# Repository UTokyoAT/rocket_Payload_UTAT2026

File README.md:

# rocket_Payload_UTAT2026

輸送機班2026年度の新人研修期間中の上級生での活動。CanSatを搭載したペットボトルロケットを開発するためのリポジトリ

---

## ドキュメント

- [環境構築](docs/setup.md)（未作成）
- [書き込み方法](docs/flashing.md)（未作成）
- [制御構造・アーキテクチャ](docs/architecture.md)（未作成）
- [地上局セットアップ](docs/ground-station.md)（未作成）
- [JLCPCB 発注手順](docs/pcb-ordering.md)（未作成）

---

## ディレクトリ構造

Seeed XIAO ESP32-S3 を1枚使う構成。ミッション本体は `env:mission`（`tests/test_mission/main.cpp`）。

```
rocket_Payload_UTAT2026/
│
├── platformio.ini           # ビルド・ボード・ライブラリ設定（env:mission / env:test-* ）
│
├── include/
│   └── secrets.example.h    # Wi-Fi・MQTT接続設定のひな形（secrets.h にコピーして使う）
│
├── src/
│   ├── MotorController/     # 単純な方位PID → 左右PWMの差動
│   ├── Actuator/            # モーター制御（TB6612FNG）
│   ├── Deployer/            # ロケット分離・パラシュート分離（ニクロム線）
│   └── LED/                 # LED制御
│
├── lib/
│   ├── Encoder/             # 左右ホイールエンコーダ（ホール、A/B相の割り込みカウント）
│   ├── Expander/            # I/Oエキスパンダ（MCP23008）
│   ├── GPS/                 # TinyGPSPlus ラッパー
│   ├── KalmanFilter/        # 拡張カルマンフィルタ（EKF）
│   ├── Sensor/              # BMP280・MPU6050 ドライバ
│   └── Telemetry/           # Wi-Fi + MQTT で地上局へ送信
│
├── tests/
│   ├── test_mission/        # ミッション本体（キャリブレーション → EKF起動 → 誘導 → 停止）
│   └── test_*/              # センサー・アクチュエータ単体の動作確認（env:test-*）
│
├── matlab/
│   └── ekf_cansat_simulation/  # EKF・誘導のシミュレーション（符号規約の参照実装）
│
├── ground/
│   └── server/              # 地上局（Mosquitto・Telegraf・InfluxDB・Grafana の docker compose）
│
└── hardware/
    ├── kicad/               # KiCad プロジェクトファイル
    └── jlcpcb/
        ├── gerbers/         # Gerberファイル（発注用ZIP）
        ├── bom/             # Bill of Materials
        └── cpl/             # Component Placement List
```

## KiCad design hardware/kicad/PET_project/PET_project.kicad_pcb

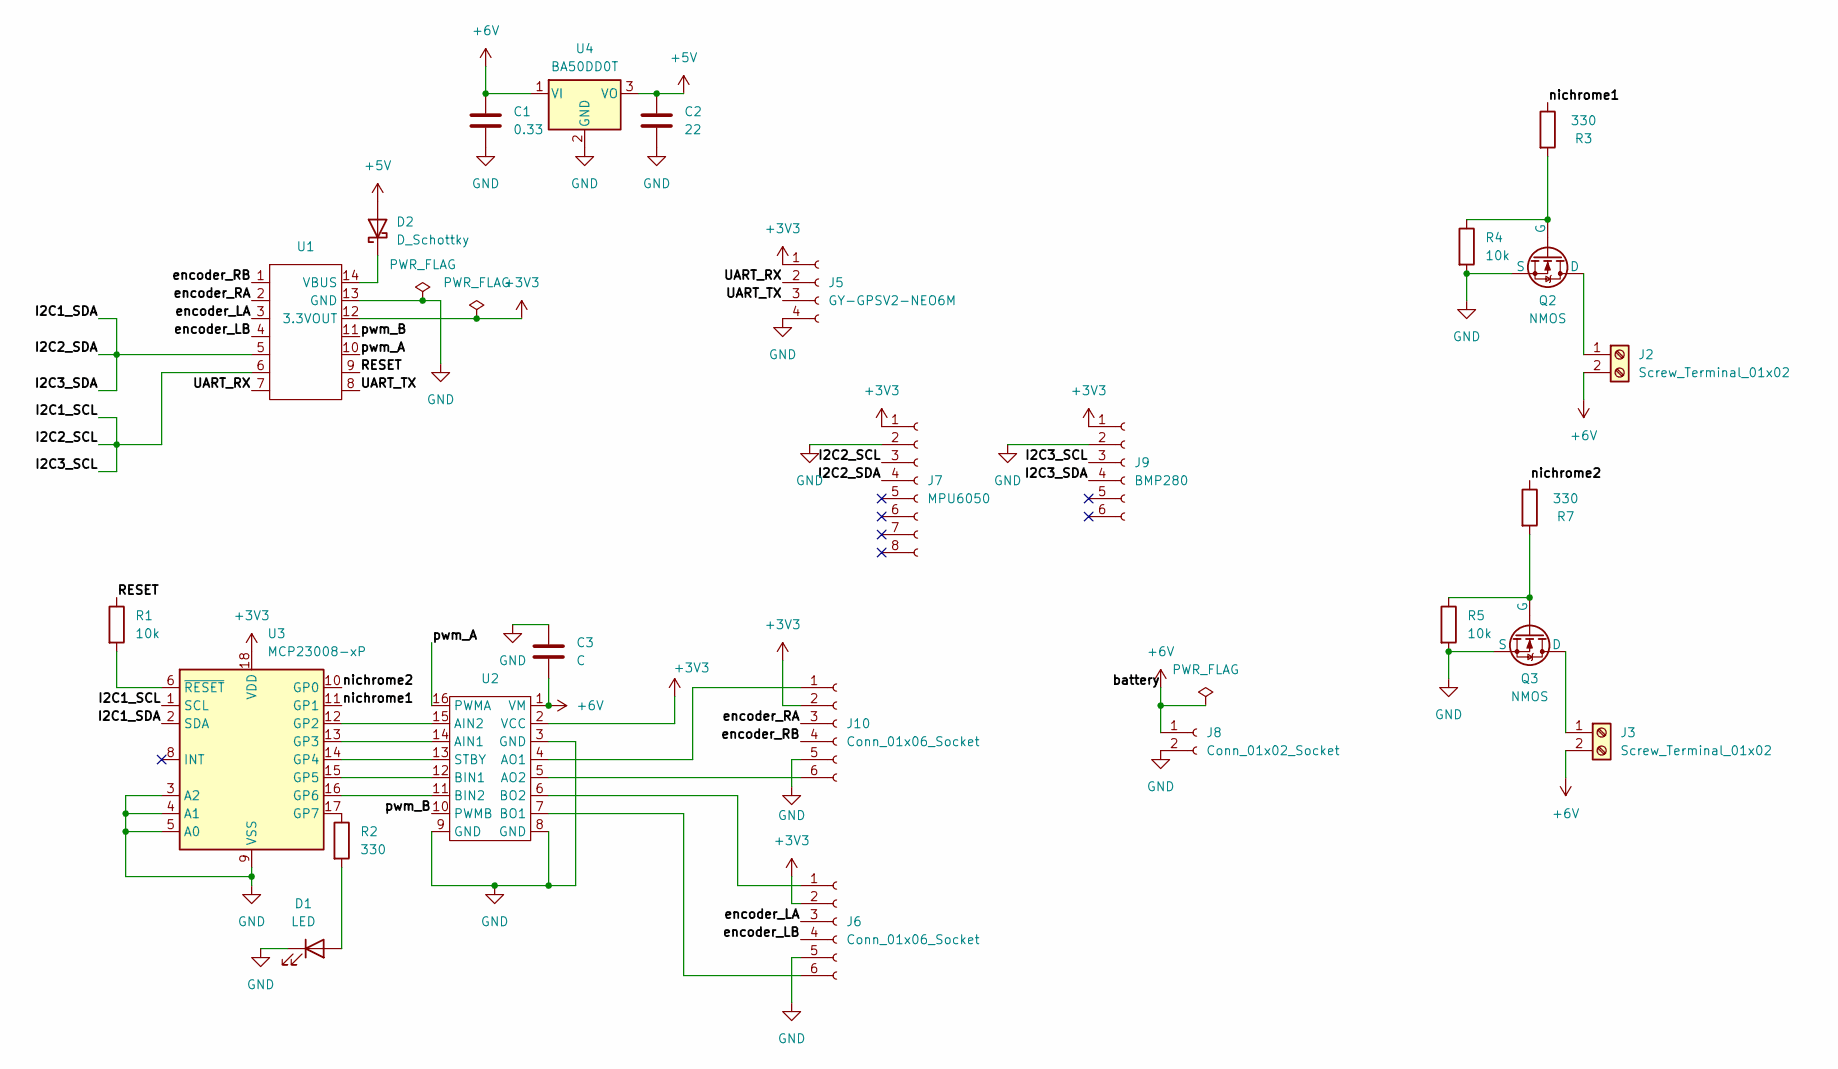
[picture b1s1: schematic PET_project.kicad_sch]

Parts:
C1: 0.33; CP_Radial_Tantal_D4.5mm_P5.00mm
C2: 22; C_Radial_D5.0mm_H11.0mm_P2.00mm
C3: C; CP_Radial_D6.3mm_P2.50mm
D1: LED; LED_D5.0mm_Clear
D2: D_Schottky; D_schottky
J2, J3: Screw_Terminal_01x02; TerminalBlock_Phoenix_MKDS-1,5-2-5.08_1x02_P5.08mm_Horizont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
J5: GY-GPSV2-NEO6M
J6, J10: Conn_01x06_Socket; JST_XH_S6B-XH-A-1_1x06_P2.50mm_Horizontal
J7: MPU6050; MPU6050_PinSocket_Vertical
J8: Conn_01x02_Socket; JST_PH_S2B-PH-K_1x02_P2.00mm_Horizontal
J9: BMP280; BMP280_PinSocket_Vertical
Q2, Q3: NMOS; TO-220-3_Vertical
R1, R4, R5: 10k; R_Axial_DIN0204_L3.6mm_D1.6mm_P2.54mm_Vertical
R2, R3, R7: 330; R_Axial_DIN0204_L3.6mm_D1.6mm_P2.54mm_Vertical
U1: XIAO-ESP32-S3-DIP
U2: TB6612FNG
U3: MCP23008-xP; DIP-18_W7.62mm
U4: BA50DD0T; TO-220-3_Vertical

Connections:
+3V3: J5.1, J6.2, J7.1, J9.1, J10.2, U1.12 (3.3VOUT), U2.2 (VCC), U3.18 (VDD)
+5V: C2.1, D2.2 (A), U4.3 (VO)
+6V: C1.1, C3.2, J2.2, J3.2, J8.1, U2.1 (VM), U4.1 (VI)
/I2C1_SCL: J7.3, J9.3, U1.6, U3.1 (SCL)
/I2C1_SDA: J7.4, J9.4, U1.5, U3.2 (SDA)
/RESET: R1.1, U1.9
/UART_RX: J5.2, U1.7
/UART_TX: J5.3, U1.8
/encoder_LA: J6.3, U1.3
/encoder_LB: J6.4, U1.4
/encoder_RA: J10.3, U1.2
/encoder_RB: J10.4, U1.1
/nichrome1: R3.1, U3.11 (GP1)
/nichrome2: R7.1, U3.10 (GP0)
/pwm_A: U1.10, U2.16 (PWMA)
/pwm_B: U1.11, U2.10 (PWMB)
GND: C1.2, C2.2, C3.1, D1.1 (K), J5.4, J6.5, J7.2, J8.2, J9.2, J10.5, Q2.3 (S), Q3.3 (S), R4.2, R5.2, U1.13 (GND), U2.3 (GND), U2.8 (GND), U2.9 (GND), U3.3 (A2), U3.4 (A1), U3.5 (A0), U3.9 (VSS), U4.2 (GND)
unnamed: D1.2 (A), R2.2
unnamed: D2.1 (K), U1.14 (VBUS)
unnamed: J2.1, Q2.1 (D)
unnamed: J3.1, Q3.1 (D)
unnamed: J6.1, U2.6 (BO2)
unnamed: J6.6, U2.7 (BO1)
unnamed: J10.1, U2.4 (AO1)
unnamed: J10.6, U2.5 (AO2)
unnamed: Q2.2 (G), R3.2, R4.1
unnamed: Q3.2 (G), R5.1, R7.2
unnamed: U2.14 (AIN1), U3.13 (GP3)
unnamed: U2.15 (AIN2), U3.12 (GP2)
unnamed: U2.12 (BIN1), U3.15 (GP5)
unnamed: U2.11 (BIN2), U3.16 (GP6)
unnamed: U2.13 (STBY), U3.14 (GP4)
unnamed: R2.1, U3.17 (GP7)
unnamed: R1.2, U3.6 (~RESET)

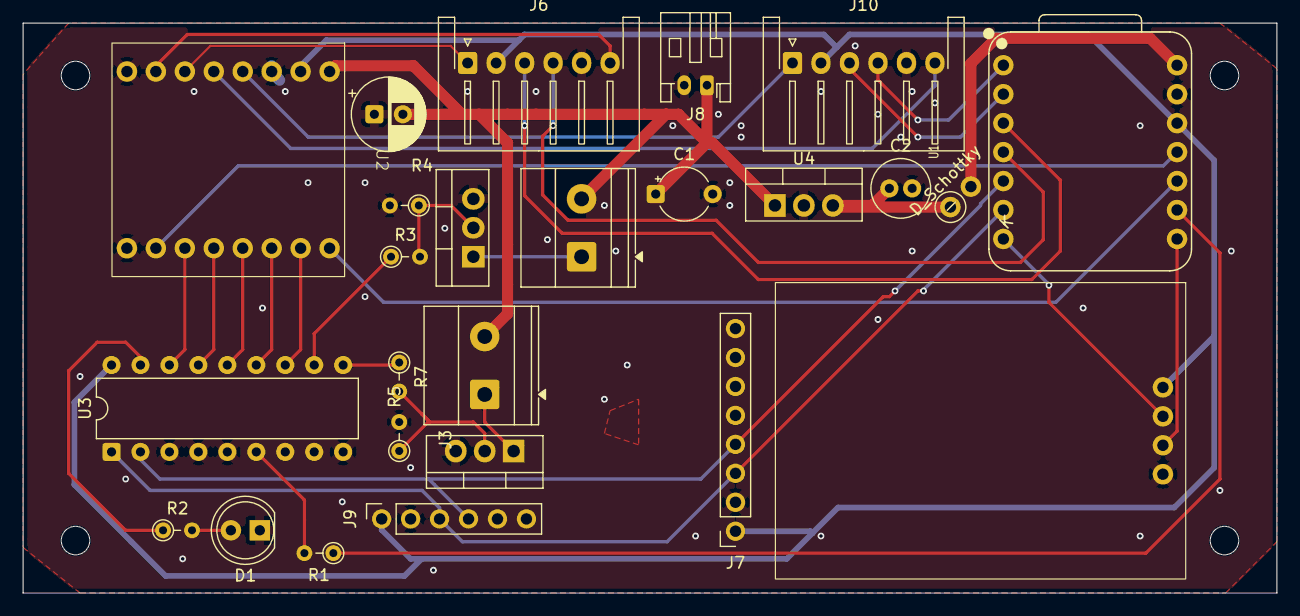
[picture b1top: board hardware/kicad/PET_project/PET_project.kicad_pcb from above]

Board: 2 copper layers, 110.0 x 50.0 mm, 25 parts (0 on the bottom side), 34 nets.

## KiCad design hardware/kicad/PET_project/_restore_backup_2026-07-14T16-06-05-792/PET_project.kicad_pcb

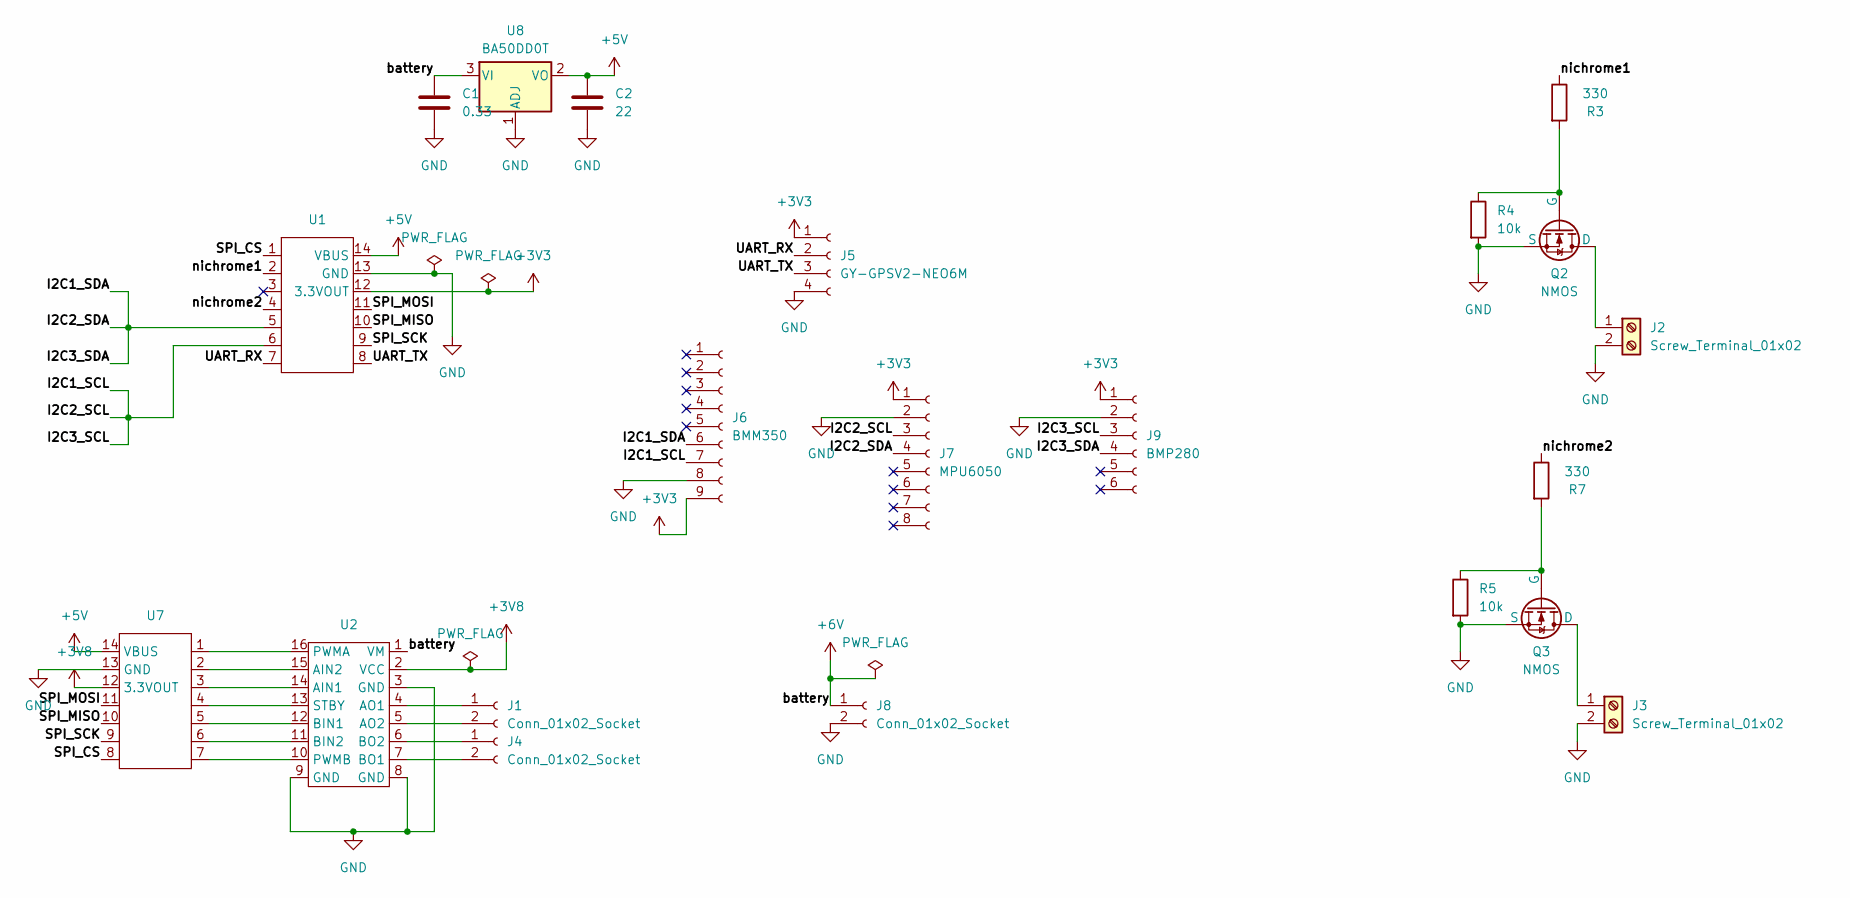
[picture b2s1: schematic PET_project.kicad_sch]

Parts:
C1: 0.33; CP_Radial_Tantal_D4.5mm_P5.00mm
C2: 22; C_Radial_D5.0mm_H11.0mm_P2.00mm
J1, J4: Conn_01x02_Socket; JST_XH_S2B-XH-A_1x02_P2.50mm_Horizontal
J2, J3: Screw_Terminal_01x02; TerminalBlock_Phoenix_MKDS-1,5-2-5.08_1x02_P5.08mm_Horizont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
J5: GY-GPSV2-NEO6M
J6: BMM350; BMM350_PinSocket_Vertical
J7: MPU6050; MPU6050_PinSocket_Vertical
J8: Conn_01x02_Socket; JST_PH_S2B-PH-K_1x02_P2.00mm_Horizontal
J9: BMP280; BMP280_PinSocket_Vertical
Q2, Q3: NMOS; TO-220-3_Vertical
R3, R7: 330; R_Axial_DIN0204_L3.6mm_D1.6mm_P2.54mm_Vertical
R4, R5: 10k; R_Axial_DIN0204_L3.6mm_D1.6mm_P2.54mm_Vertical
U1, U7: XIAO-ESP32-S3-DIP
U2: TB6612FNG
U8: BA50DD0T; TO-220-3_Vertical

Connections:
+3V3: J5.1, J6.9, J7.1, J9.1, U1.12 (3.3VOUT)
+3V8: U2.2 (VCC), U7.12 (3.3VOUT)
+5V: C2.1, U1.14 (VBUS), U7.14 (VBUS), U8.2 (VO)
+6V: C1.1, J8.1, U2.1 (VM), U8.3 (VI); also elsewhere on the board
/I2C1_SCL: J6.7, J7.3, J9.3, U1.6
/I2C1_SDA: J6.6, J7.4, J9.4, U1.5
/SPI_CS: U1.1, U7.8
/SPI_MISO: U1.10, U7.10
/SPI_MOSI: U1.11, U7.11
/SPI_SCK: U1.9, U7.9
/UART_RX: J5.2, U1.7
/UART_TX: J5.3, U1.8
/nichrome1: R3.1, U1.2
/nichrome2: R7.1, U1.4
GND: C1.2, C2.2, J2.2, J3.2, J5.4, J6.8, J7.2, J8.2, J9.2, Q2.3 (S), Q3.3 (S), R4.2, R5.2, U1.13 (GND), U2.3 (GND), U2.8 (GND), U2.9 (GND), U7.13 (GND), U8.1 (ADJ); also elsewhere on the board
unnamed: J1.1, U2.4 (AO1)
unnamed: J1.2, U2.5 (AO2)
unnamed: J2.1, Q2.1 (D)
unnamed: J3.1, Q3.1 (D)
unnamed: J4.1, U2.6 (BO2)
unnamed: J4.2, U2.7 (BO1)
unnamed: Q2.2 (G), R3.2, R4.1
unnamed: Q3.2 (G), R5.1, R7.2
unnamed: U2.14 (AIN1), U7.3
unnamed: U2.15 (AIN2), U7.2
unnamed: U2.12 (BIN1), U7.5
unnamed: U2.11 (BIN2), U7.6
unnamed: U2.16 (PWMA), U7.1
unnamed: U2.10 (PWMB), U7.7
unnamed: U2.13 (STBY), U7.4

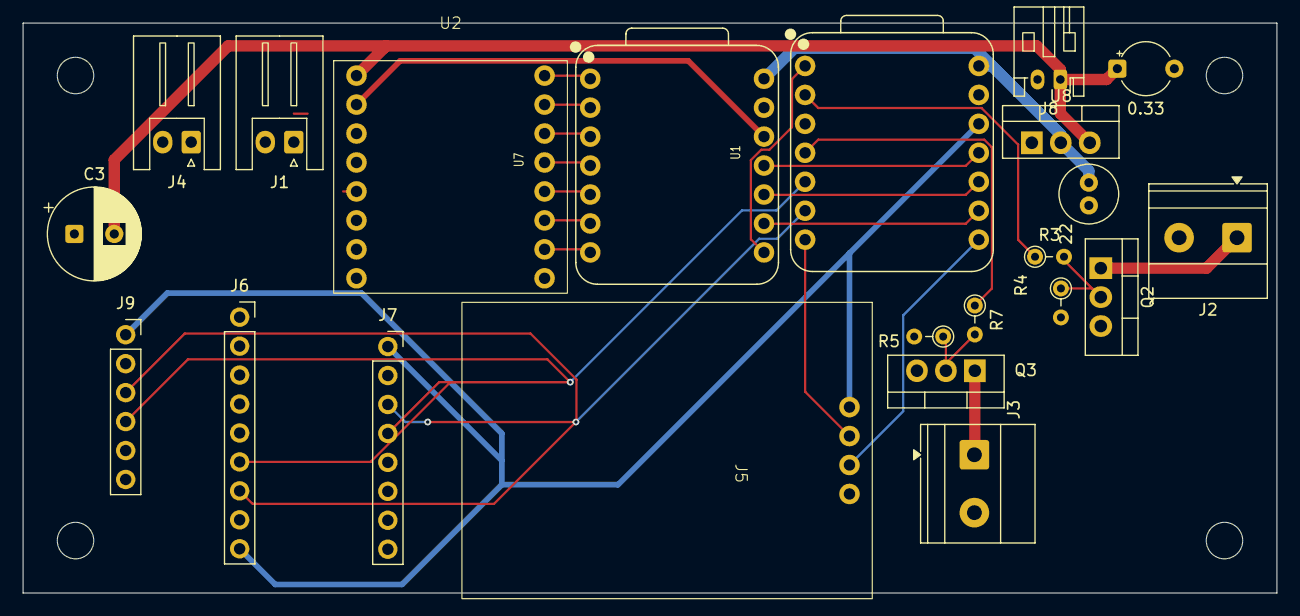
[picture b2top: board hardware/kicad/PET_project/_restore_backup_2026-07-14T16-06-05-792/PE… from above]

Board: 2 copper layers, 110.0 x 50.0 mm, 22 parts (0 on the bottom side), 30 nets.

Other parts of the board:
C3: C; CP_Radial_D8.0mm_P3.50mm

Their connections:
+6V: C3.2; also elsewhere on the board
GND: C3.1; also elsewhere on the board

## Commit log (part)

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2026-06-25 開発のセットアップ
2026-06-25 hardwareのためのセットアップ
2026-06-25 セットアップ②
2026-06-25 地上局のセットアップ
2026-06-26 テストコード
